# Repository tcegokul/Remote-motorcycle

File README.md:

# Modular Remote Control System for Motorcycle

## Overview

This project is a modular remote control system designed to interface with a motorcycle's main MCU board. The remote module is built using an ESP32 microcontroller and communicates with the main board via Bluetooth. An e-paper display is integrated to provide real-time status updates and control feedback, making it a user-friendly and efficient control interface for two-wheeler embedded systems.

## Features

- ESP32-based microcontroller
- Bluetooth communication with the main MCU board
- E-paper display for control status and feedback
- Powered by 12V, compatible with standard motorcycle electrical systems

## Software Tools

- **KiCAD Version:** 8.0
- **External Libraries:** Most of the component libraries used in this project are sourced from Ultra Librarian. Refer to the `libraries/` section for more details.

## Fabrication

**Note:** This design has not been fabricated yet. If you plan to fabricate the PCB, make sure to thoroughly check the schematic and PCB layout before proceeding to production.

## Contact

**Name:** Gokul Rajaram  
**Email:** gokulrajarama@gmail.com  
**Phone:** +91 9025938754

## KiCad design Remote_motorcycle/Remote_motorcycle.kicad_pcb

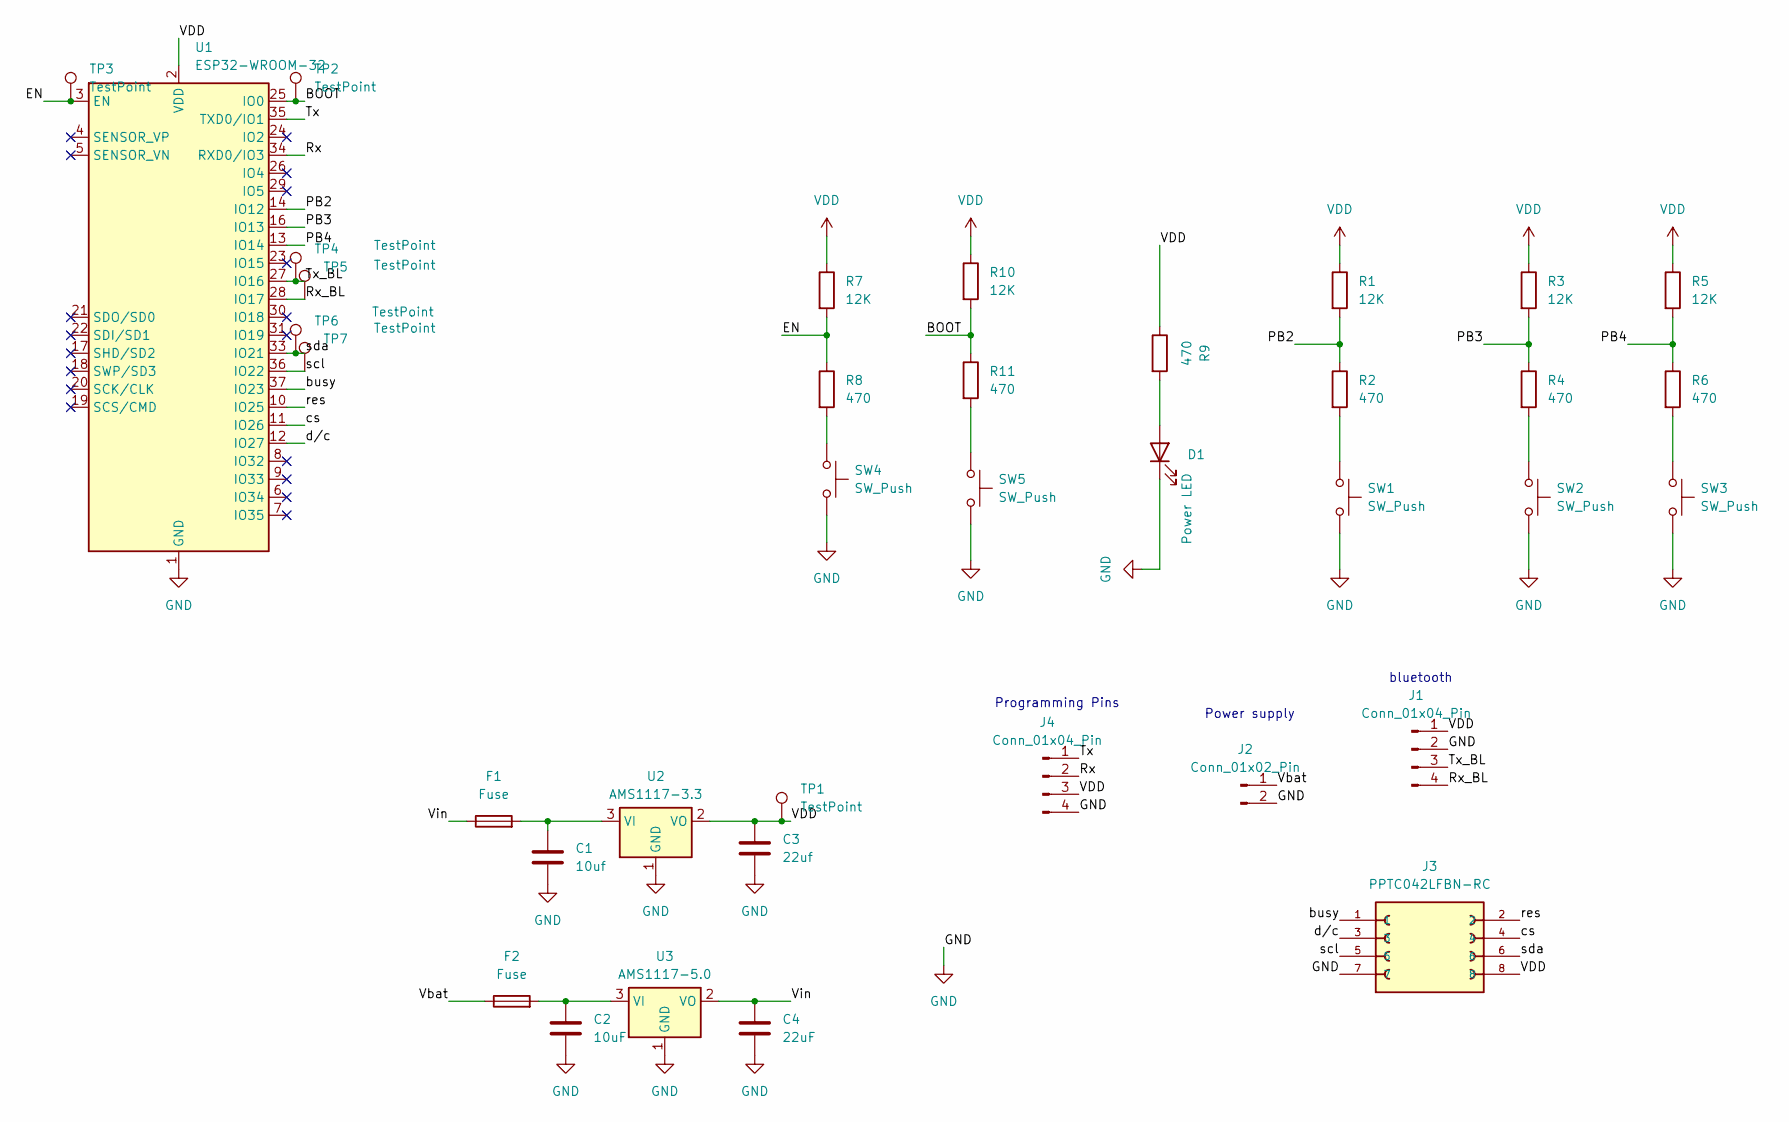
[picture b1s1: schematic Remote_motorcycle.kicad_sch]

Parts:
C1: 10uf; C_0603_1608Metric_Pad1.08x0.95mm_HandSolder
C2: 10uF; C_0603_1608Metric_Pad1.08x0.95mm_HandSolder
C3: 22uf; C_0603_1608Metric_Pad1.08x0.95mm_HandSolder
C4: 22uF; C_0603_1608Metric_Pad1.08x0.95mm_HandSolder
D1: Power LED; LED_0603_1608Metric_Pad1.05x0.95mm_HandSolder
F1, F2: Fuse; Fuse_1206_3216Metric_Pad1.42x1.75mm_HandSolder
J1: Conn_01x04_Pin; PinSocket_1x04_P2.54mm_Horizontal
J2: Conn_01x02_Pin; TE_282837-2
J3: PPTC042LFBN-RC; SULLINS_PPTC042LFBN-RC; PARTREV L
J4: Conn_01x04_Pin; PinSocket_1x04_P2.54mm_Vertical
R1, R3, R5, R7, R10: 12K; R_0805_2012Metric_Pad1.20x1.40mm_HandSolder
R2, R4, R6, R8, R9, R11: 470; R_0805_2012Metric_Pad1.20x1.40mm_HandSolder
SW1, SW2, SW3, SW4, SW5: SW_Push; SW_Push_1P1T_NO_6x6mm_H9.5mm
TP1, TP2, TP3, TP4, TP5, TP6, TP7: TestPoint; TestPoint_Pad_1.5x1.5mm
U1: ESP32-WROOM-32
U2: AMS1117-3.3; SOT-223-3_TabPin2
U3: AMS1117-5.0; SOT-223-3_TabPin2

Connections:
/BOOT: R10.2, R11.1, TP2.1, U1.25 (IO0)
/EN: R7.2, R8.1, TP3.1, U1.3 (EN)
/PB2: R1.2, R2.1, U1.14 (IO12)
/PB3: R3.2, R4.1, U1.16 (IO13)
/PB4: R5.2, R6.1, U1.13 (IO14)
/Rx: J4.2, U1.34 (RXD0/IO3)
/Rx_BL: J1.4, TP5.1, U1.28 (IO17)
/Tx: J4.1, U1.35 (TXD0/IO1)
/Tx_BL: J1.3, TP4.1, U1.27 (IO16)
/Vbat: F2.1, J2.1
/Vin: C4.1, F1.1, U3.2 (VO)
/busy: J3.1, U1.37 (IO23)
/cs: J3.4, U1.11 (IO26)
/d/c: J3.3, U1.12 (IO27)
/res: J3.2, U1.10 (IO25)
/scl: J3.5, TP7.1, U1.36 (IO22)
/sda: J3.6, TP6.1, U1.33 (IO21)
GND: C1.2, C2.2, C3.2, C4.2, D1.1 (K), J1.2, J2.2, J3.7, J4.4, SW1.2, SW2.2, SW3.2, SW4.2, SW5.2, U1.1 (GND), U1.15 (GND), U1.38 (GND), U1.39 (GND), U2.1 (GND), U3.1 (GND)
unnamed: D1.2 (A), R9.2
unnamed: R2.2, SW1.1
unnamed: R4.2, SW2.1
unnamed: R6.2, SW3.1
unnamed: R8.2, SW4.1
unnamed: R11.2, SW5.1
unnamed: C1.1, F1.2, U2.3 (VI)
unnamed: C2.1, F2.2, U3.3 (VI)
VDD: C3.1, J1.1, J3.8, J4.3, R1.1, R3.1, R5.1, R7.1, R9.1, R10.1, TP1.1, U1.2 (VDD), U2.2 (VO)

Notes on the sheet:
Programming Pins
Power supply
bluetooth

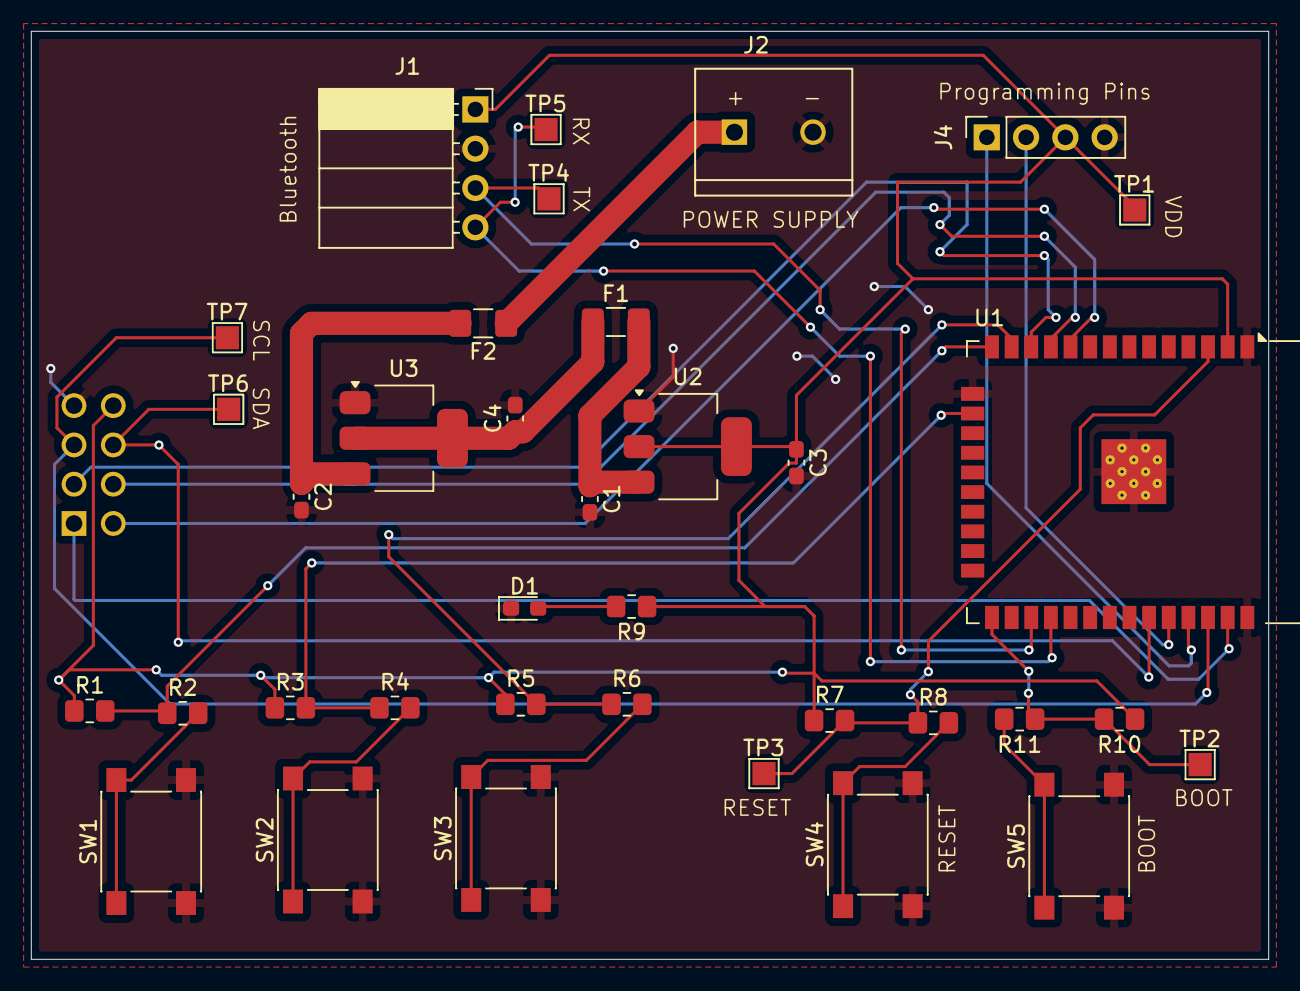
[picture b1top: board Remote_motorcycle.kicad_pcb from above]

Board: 2 copper layers, 80.0 x 60.0 mm, 37 parts (1 on the bottom side), 27 nets.
